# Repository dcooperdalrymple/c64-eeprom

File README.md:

# C64-EEPROM

Use standard 0.6" DIP EEPROMs in place of a mask rom footprints. Compatible with various mask roms and EEPROMS with solder jumper configuration.

| Top                                       | Bottom                                          |
| ----------------------------------------- | ----------------------------------------------- |
|  |  |

## Compatible ROM ICs

Use the following tables to determine the necessary solder jumper configuration.

### EEPROMs

| EEPROM      | Configuration                                                                                             |
| ----------- | --------------------------------------------------------------------------------------------------------- |
| AT28C64(B)  | A13 and A14 jumpers can be left unconfigured (NC).                                                        |
| AT28C256    | A13 and A14 jumpers can be configured to select 1 of 4 banks. Leave both as "0" (GND) to use first 4/8KB. |

> It is possible to connect switches to the A13 and A14 solder jumper pads to enable quick bank switching with an AT28C256 to select between 4 ROM images. To minimize size and materials, this board does not include this feature by default.

### Mask ROMs

| Mask ROM    | Typical Usage                                   | Configuration                                                                                 |
| ----------- | ----------------------------------------------- | --------------------------------------------------------------------------------------------- |
| 2364        | C64 Kernal (901227-03) & BASIC (901226-01) ROMs | Solder pad 2 (middle) to pad 1 (arrow) of the 64/32 jumper (the 64 side) and the OE jumper.   |
| 2332        | C64 Character ROM (901225-01)                   | Solder pad 2 (middle) to pad 3 (bottom) of the 64/32 jumper (the 32 side) and the A12 jumper. |

## Materials

This board uses 2 SMD 0.1" pitch pin headers and 1 0.6" wide, 0.1" pitch SMD DIP socket. SMD components were selected to reduce board width. However, standard through hole components can be easily modified to be SMD compatible by bending the socket legs outward and the pin header legs left and right alternating outward.

No other components are necessary as the AT28C64/256 EEPROMS are 5V-compatible and otherwise identical to standard mask roms. Using this board without an IC socket for the EEPROM is possible, but not recommended.

## Programming

EEPROMs are fairly simple and easy to program. They can be programmed using a standard TL866 programmer or any other compatible ROM programmer. A number of other solutions also exist which don't require specialized equipment. Here are a few options using off-the-shelf components:

- [PicoPROM](https://github.com/gfoot/picoprom)
- [32u4-programmer](https://github.com/dcooperdalrymple/32u4-programmer) (a little bit of self-promotion here)
- [Arduino EEPROM programmer](https://github.com/beneater/eeprom-programmer)
- [eeprom-writer](https://github.com/oddblk/eeprom-writer)
- [TommyPROM](https://tomnisbet.github.io/TommyPROM/)

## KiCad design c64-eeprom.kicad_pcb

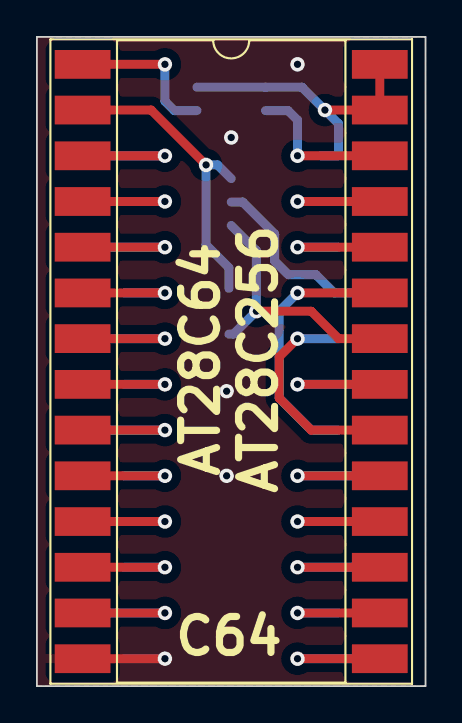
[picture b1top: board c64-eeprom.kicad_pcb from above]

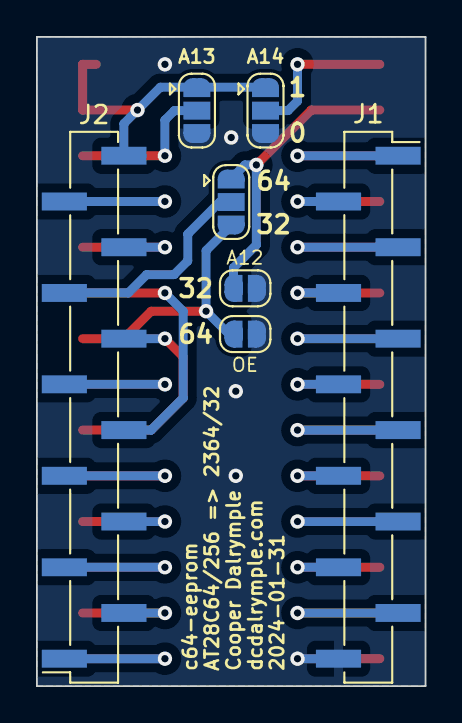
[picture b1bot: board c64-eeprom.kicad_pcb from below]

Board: 2 copper layers, 21.6 x 36.1 mm, 8 parts (7 on the bottom side), 28 nets.

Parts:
J1, J2: Conn_01x12_Pin; PinHeader_1x12_P2.54mm_Vertical_SMD_Pin1Right
JP1, JP2: Jumper_3_Open; SolderJumper-3_P1.3mm_Open_RoundedPad1.0x1.5mm
JP3: A12_GND; SolderJumper-2_P1.3mm_Open_RoundedPad1.0x1.5mm
JP4: A12/CS2; SolderJumper-3_P1.3mm_Open_RoundedPad1.0x1.5mm
JP5: OE_GND; SolderJumper-2_P1.3mm_Open_RoundedPad1.0x1.5mm
U2: DIP-28_W16.51mm_SMDSocket_LongPads

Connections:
GND: J1.12, JP1.3 (B), JP2.3 (B), JP3.2 (B), JP5.2 (B), U2.14 (GND)
unnamed: J1.1, U2.3 (A7)
unnamed: J1.2, U2.4 (A6)
unnamed: J1.3, U2.5 (A5)
unnamed: J1.4, U2.6 (A4)
unnamed: J1.5, U2.7 (A3)
unnamed: J1.6, U2.8 (A2)
unnamed: J1.7, U2.9 (A1)
unnamed: J1.8, U2.10 (A0)
unnamed: J1.9, U2.11 (I/O0)
unnamed: J1.10, U2.12 (I/O1)
unnamed: J1.11, U2.13 (I/O2)
unnamed: J2.1, U2.15 (I/O3)
unnamed: J2.2, U2.16 (I/O4)
unnamed: J2.3, U2.17 (I/O5)
unnamed: J2.4, U2.18 (I/O6)
unnamed: J2.5, U2.19 (I/O7)
unnamed: J2.6, U2.23 (A11)
unnamed: J2.7, U2.21 (A10)
unnamed: J2.8, U2.20 (CE)
unnamed: J2.9, JP4.2 (C)
unnamed: J2.10, U2.24 (A9)
unnamed: J2.11, U2.25 (A8)
unnamed: JP1.2 (C), U2.1 (NC/A14)
unnamed: JP2.2 (C), U2.26 (NC/A13)
unnamed: JP3.1 (A), JP4.1 (A), U2.2 (A12)
unnamed: JP4.3 (B), JP5.1 (A), U2.22 (OE)
VCC: J2.12, JP1.1 (A), JP2.1 (A), U2.27 (WE), U2.28 (VCC)

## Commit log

2024-02-01 Initial design.
2024-02-01 Added simple 3d views
2024-02-01 Added schematic PDF
2024-02-01 Added silkscreen to top to indicate compatible eeproms.
2024-02-01 Updated gitignore to remove generated gerber files.
2024-02-01 Added README.
2024-02-15 Fix disconnected jumper pad, A12.
2024-02-27 Added Tindie store badge to README.
